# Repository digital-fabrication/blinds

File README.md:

# blinds
Principles of Digital Fabrication, University of Oulu

## Links

- Blinds frame boxes.py url https://www.festi.info/boxes.py/ClosedBox?FingerJoint_angle=90.0&FingerJoint_surroundingspaces=2.0&FingerJoint_edge_width=1.0&FingerJoint_finger=2.0&FingerJoint_play=0.0&FingerJoint_space=2.0&FingerJoint_width=1.0&x=450.0&y=50.0&h=440.0&outside=0&thickness=3.0&format=svg&tabs=0.0&debug=0&reference=100&burn=0.1&render=1
- Manual install instructions for esp32 on Windows (might be useful if you do not have administrative access rights) https://github.com/espressif/arduino-esp32/blob/master/docs/arduino-ide/windows.md

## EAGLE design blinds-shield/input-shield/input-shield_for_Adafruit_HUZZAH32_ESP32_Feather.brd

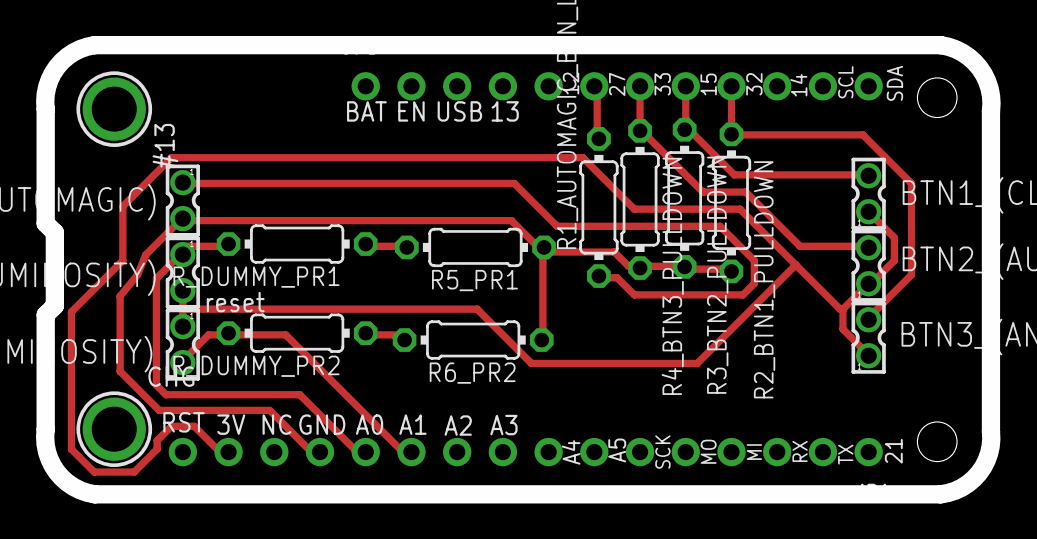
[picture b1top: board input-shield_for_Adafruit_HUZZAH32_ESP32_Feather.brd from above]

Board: 2 copper layers, 52.6 x 25.0 mm, 18 parts (0 on the bottom side), 11 nets.

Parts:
BTN1_(CLOCKWIZE), BTN2_(AUTOMAGIC), BTN3_(ANTICLOCKWIZE): 332-02
JP1: 1X16_ROUND_MIN
JP3: 1X12_ROUND_MIN
LED_(AUTOMAGIC): 332-02
PR1_(LUMINOSITY), PR2_(LUMINOSITY): 332-02
R1_AUTOMAGIC_BTN_LED: 165Ω; 0204/7
R2_BTN1_PULLDOWN, R3_BTN2_PULLDOWN, R4_BTN3_PULLDOWN: 1kΩ; 0204/7
R5_PR1, R6_PR2: 4k ohm; 0204/7
R_DUMMY_PR1, R_DUMMY_PR2: 0k ohm; 0204/7
U$31, U$32: MOUNTINGHOLE2.5; MOUNTINGHOLE_2.5_PLATED

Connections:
3.3V: BTN1_(CLOCKWIZE).1, BTN2_(AUTOMAGIC).1, BTN3_(ANTICLOCKWIZE).1, JP1.15, PR1_(LUMINOSITY).2, PR2_(LUMINOSITY).1
A0_DAC2: JP1.12, PR1_(LUMINOSITY).1, R_DUMMY_PR1.2
A1_DAC1: JP1.11, PR2_(LUMINOSITY).2, R_DUMMY_PR2.2
GND: JP1.13, LED_(AUTOMAGIC).2, R2_BTN1_PULLDOWN.2, R3_BTN2_PULLDOWN.2, R4_BTN3_PULLDOWN.2, R5_PR1.1, R6_PR2.1
IO15_A8: BTN1_(CLOCKWIZE).2, JP3.8, R3_BTN2_PULLDOWN.1
IO27_A10: JP3.6, R1_AUTOMAGIC_BTN_LED.2
IO32_A7: BTN3_(ANTICLOCKWIZE).2, JP3.9, R2_BTN1_PULLDOWN.1
IO33_A9: BTN2_(AUTOMAGIC).2, JP3.7, R4_BTN3_PULLDOWN.1
unnamed: LED_(AUTOMAGIC).1, R1_AUTOMAGIC_BTN_LED.1
unnamed: R5_PR1.2, R_DUMMY_PR1.1
unnamed: R6_PR2.2, R_DUMMY_PR2.1

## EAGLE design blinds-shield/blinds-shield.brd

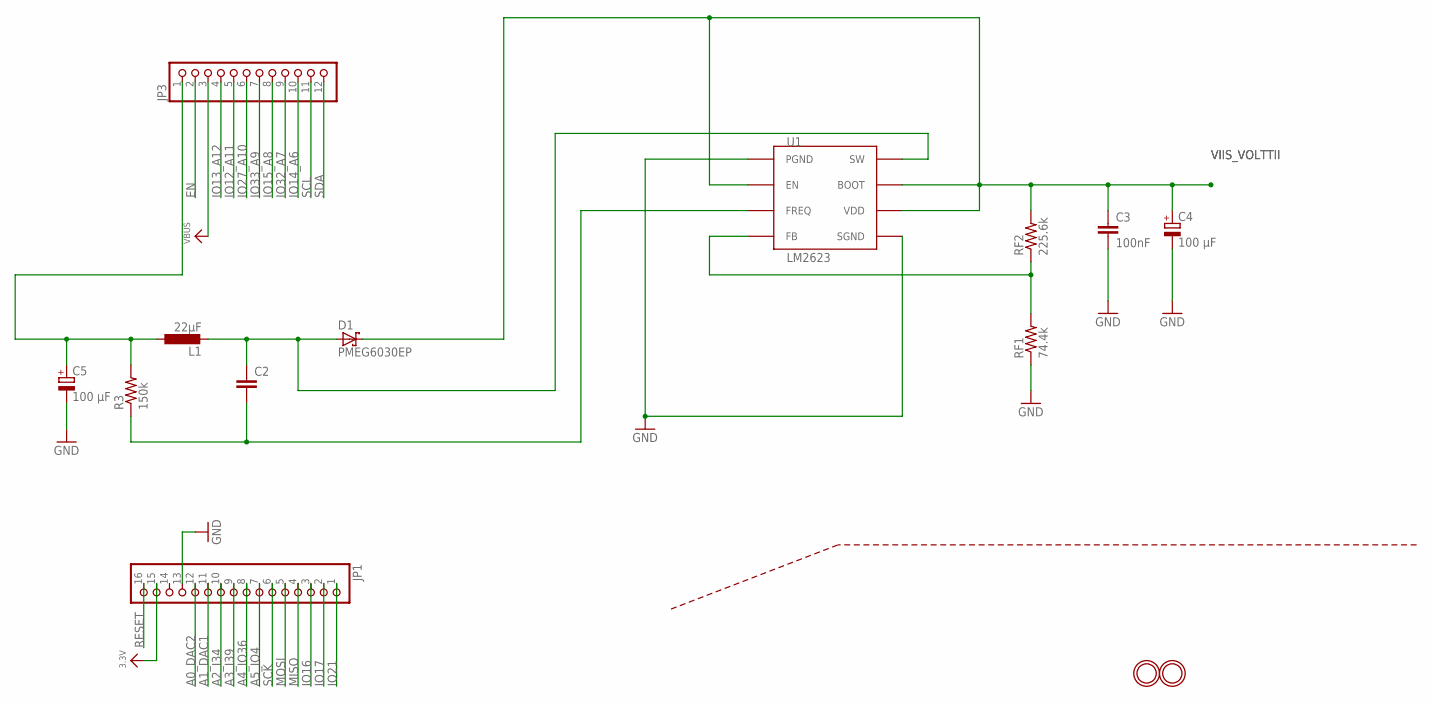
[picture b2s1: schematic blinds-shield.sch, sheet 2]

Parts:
C2: C-EU025-060X050; C025-060X050
C3: 100nF; C025-060X050
C4, C5: 100 µF; 085CS_1AR
D1: PMEG6030EP; SOD128
JP1: HEADER-1X16_MIN; 1X16_ROUND_MIN
JP3: HEADER-1X12_MIN; 1X12_ROUND_MIN
L1: 22µF; L5650M
R3: 150k; R5025
RF1: 74.4k; R5025
RF2: 225.6k; R5025
U1: LM2623; VSSOP8
U$31, U$32: MOUNTINGHOLE2.5; MOUNTINGHOLE_2.5_PLATED

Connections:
3.3V: JP1.15
A0_DAC2: JP1.12
A1_DAC1: JP1.11
A2_I34: JP1.10
A3_I39: JP1.9
A4_IO36: JP1.8
A5_IO4: JP1.7
EN: JP3.2
GND: C3.2, C4.-, C5.-, JP1.13, RF1.1, U1.PGND, U1.SGND
IO12_A11: JP3.5
IO13_A12: JP3.4
IO14_A6: JP3.10
IO15_A8: JP3.8
IO16: JP1.3
IO17: JP1.2
IO21: JP1.1
IO27_A10: JP3.6
IO32_A7: JP3.9
IO33_A9: JP3.7
MISO: JP1.4
MOSI: JP1.5
unnamed: C5.+, JP3.1, L1.1, R3.2
unnamed: C2.1, D1.2 (A), L1.2, U1.SW
unnamed: C2.2, R3.1, U1.FREQ
unnamed: RF1.2, RF2.1, U1.FB
RESET: JP1.16
SCK: JP1.6
SCL: JP3.11
SDA: JP3.12
VBUS: JP3.3
VIIS_VOLTTII: C3.1, C4.+, D1.1 (K), RF2.2, U1.BOOT, U1.EN, U1.VDD

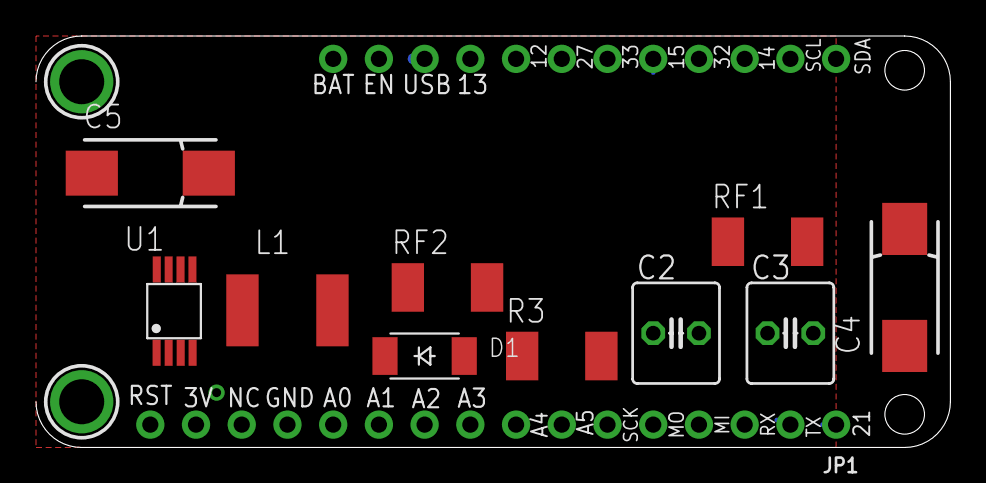
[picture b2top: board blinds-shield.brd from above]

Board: 2 copper layers, 50.8 x 22.9 mm, 14 parts (0 on the bottom side), 6 nets.

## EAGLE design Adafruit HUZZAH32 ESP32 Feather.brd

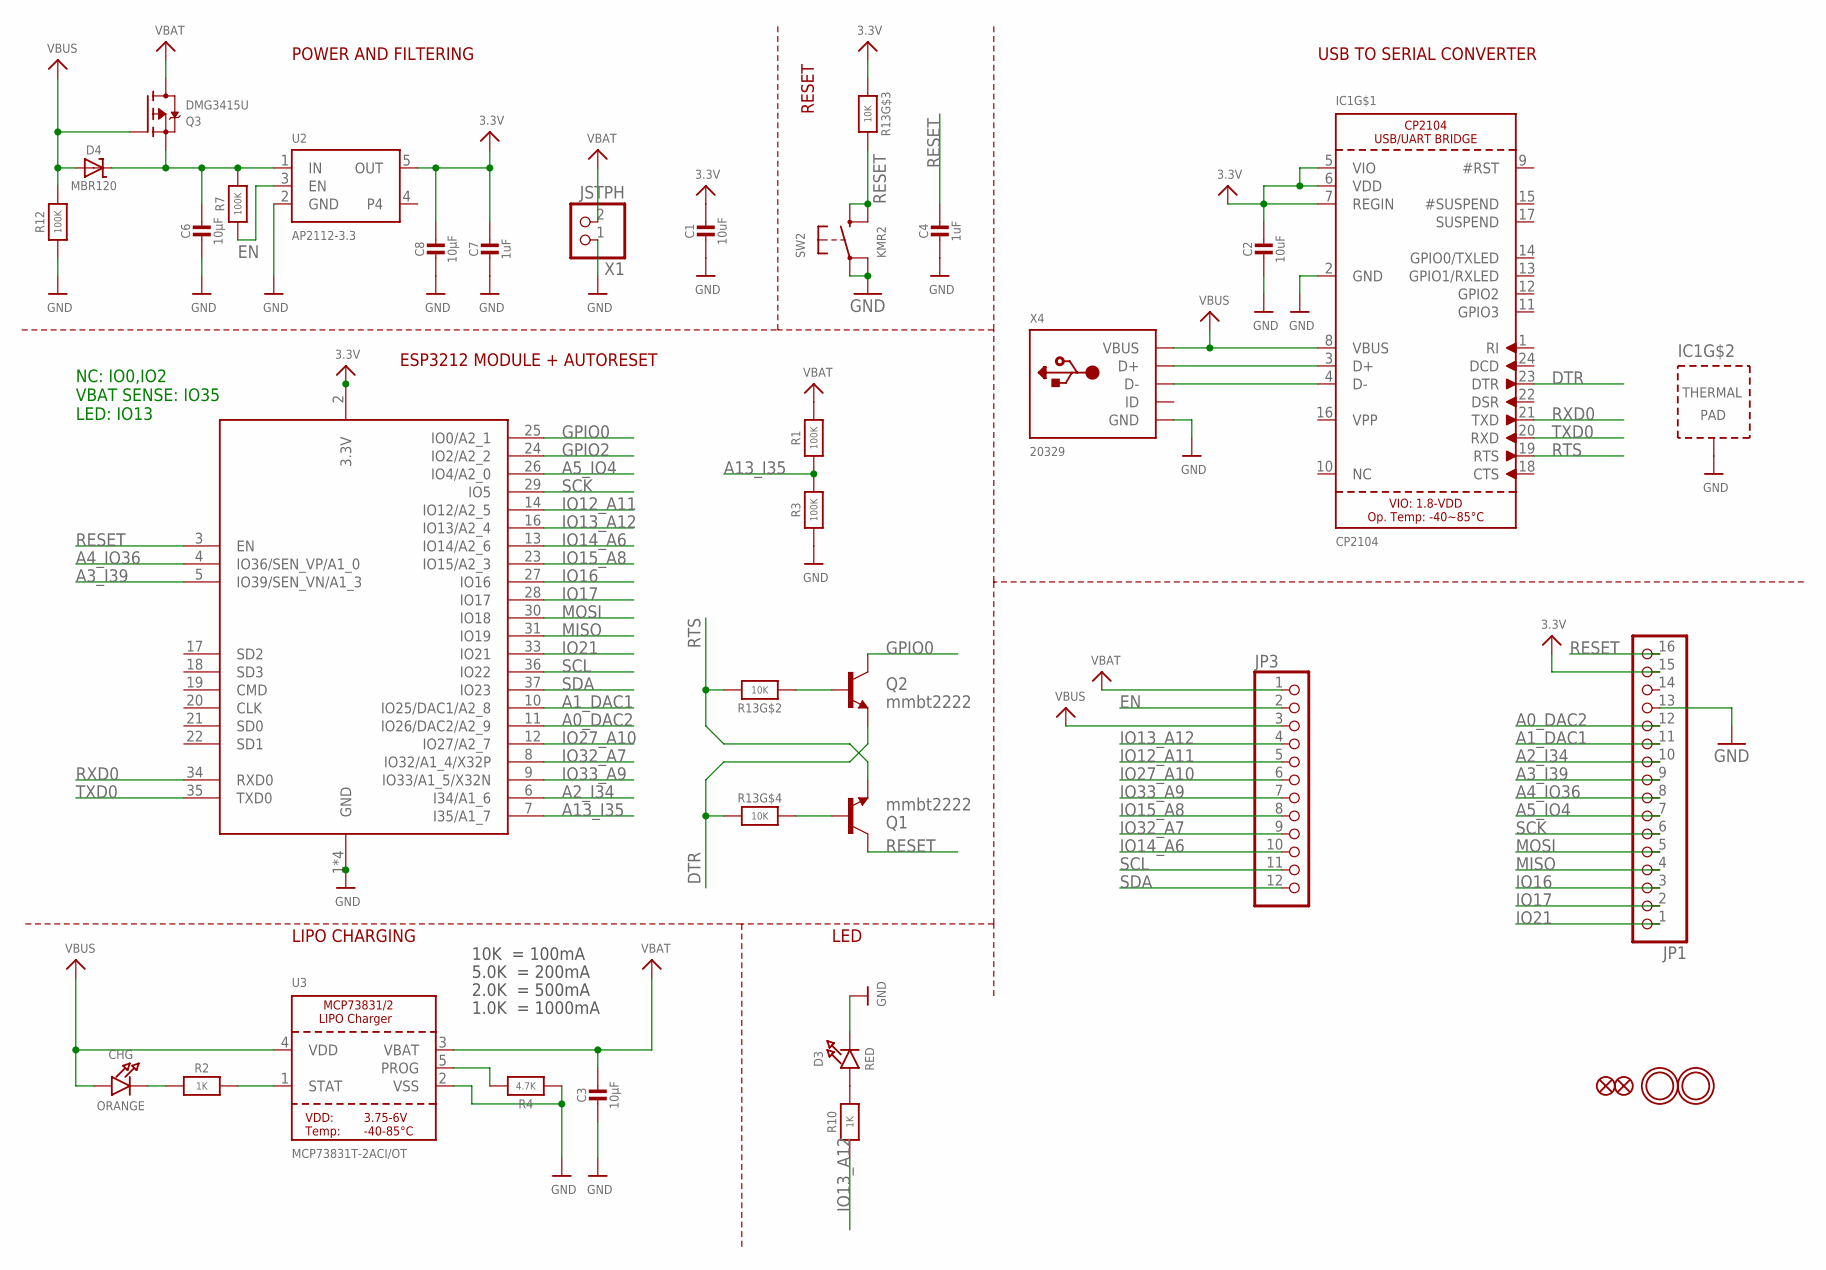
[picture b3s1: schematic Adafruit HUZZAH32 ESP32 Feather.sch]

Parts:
C1, C2: 10uF; 0805-NO
C3, C6, C8: 10µF; 0805-NO
C4, C7: 1uF; 0603-NO
CHG: ORANGE; CHIPLED_0805_NOOUTLINE
D3: RED; CHIPLED_0805_NOOUTLINE
D4: MBR120; SOD-123
IC1: CP2104; QFN24_4MM_SMSC
JP1: HEADER-1X16_MIN; 1X16_ROUND_MIN
JP3: HEADER-1X12_MIN; 1X12_ROUND_MIN
Q1, Q2: mmbt2222; SOT23-3
Q3: DMG3415U; SOT23-R
R1, R3, R7, R12: 100K; 0603-NO
R2, R10: 1K; 0603-NO
R4: 4.7K; 0603-NO
R13: 10K; RESPACK_4X0603
SW2: KMR2; BTN_KMR2_4.6X2.8
U2: AP2112-3.3; SOT23-5
U3: MCP73831T-2ACI/OT; SOT23-5
U$31, U$32: MOUNTINGHOLE2.5; MOUNTINGHOLE_2.5_PLATED
U$34, U$35: FIDUCIAL_1MM
X1: JSTPH; JSTPH2
X2: ESP32_WROOM32_SKINNY; WROOM32_SKINNY
X4: 20329; 4UCONN_20329_V2

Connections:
3.3V: C1.1, C2.1, C7.1, C8.1, IC1.5 (VIO), IC1.6 (VDD), IC1.7 (REGIN), JP1.15, R13.3 (1), U2.5 (OUT), X2.2 (3.3V)
A0_DAC2: JP1.12, X2.11 (IO26/DAC2/A2_9)
A1_DAC1: JP1.11, X2.10 (IO25/DAC1/A2_8)
A2_I34: JP1.10, X2.6 (I34/A1_6)
A3_I39: JP1.9, X2.5 (IO39/SEN_VN/A1_3)
A4_IO36: JP1.8, X2.4 (IO36/SEN_VP/A1_0)
A5_IO4: JP1.7, X2.26 (IO4/A2_0)
A13_I35: R1.1, R3.2, X2.7 (I35/A1_7)
DTR: IC1.23 (DTR), Q2.2 (E), R13.4 (1)
EN: JP3.2, R7.1, U2.3 (EN)
GND: C1.2, C2.2, C3.2, C4.2, C6.2, C7.2, C8.2, D3.C, IC1.2 (GND), IC1.THERM (TP), JP1.13, R3.1, R4.1, R12.1, SW2.A, SW2.A' (P1), U2.2 (GND), U3.2 (VSS), X1.1, X2.1 (GND), X2.15 (GND), X2.38 (GND), X2.P$1 (GND), X4.BASE@1 (GND), X4.BASE@2 (GND), X4.GND, X4.SPRT@1 (GND), X4.SPRT@2 (GND), X4.SPRT@3 (GND), X4.SPRT@4 (GND)
GPIO0: Q2.3 (C), X2.25 (IO0/A2_1)
GPIO2: X2.24 (IO2/A2_2)
IO12_A11: JP3.5, X2.14 (IO12/A2_5)
IO13_A12: JP3.4, R10.1, X2.16 (IO13/A2_4)
IO14_A6: JP3.10, X2.13 (IO14/A2_6)
IO15_A8: JP3.8, X2.23 (IO15/A2_3)
IO16: JP1.3, X2.27 (IO16)
IO17: JP1.2, X2.28 (IO17)
IO21: JP1.1, X2.33 (IO21)
IO27_A10: JP3.6, X2.12 (IO27/A2_7)
IO32_A7: JP3.9, X2.8 (IO32/A1_4/X32P)
IO33_A9: JP3.7, X2.9 (IO33/A1_5/X32N)
MISO: JP1.4, X2.31 (IO19)
MOSI: JP1.5, X2.30 (IO18)
unnamed: CHG.C, R2.1
unnamed: IC1.3 (D+), X4.D+
unnamed: R2.2, U3.1 (STAT)
unnamed: R4.2, U3.5 (PROG)
unnamed: D3.A, R10.2
unnamed: IC1.4 (D-), X4.D-
unnamed: C6.1, D4.C, Q3.2 (S), R7.2, U2.1 (IN)
unnamed: Q1.1 (B), R13.5 (2)
unnamed: Q2.1 (B), R13.2 (1)
RESET: C4.1, JP1.16, Q1.3 (C), R13.6 (2), SW2.B (S), SW2.B' (S1), X2.3 (EN)
RTS: IC1.19 (RTS), Q1.2 (E), R13.7 (2)
RXD0: IC1.21 (TXD), X2.34 (RXD0)
SCK: JP1.6, X2.29 (IO5)
SCL: JP3.11, X2.36 (IO22)
SDA: JP3.12, X2.37 (IO23)
TXD0: IC1.20 (RXD), X2.35 (TXD0)
VBAT: C3.1, JP3.1, Q3.3 (D), R1.2, U3.3 (VBAT), X1.2
VBUS: CHG.A, D4.A, IC1.8 (VBUS), JP3.3, Q3.1 (G), R12.2, U3.4 (VDD), X4.VBUS

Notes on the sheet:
POWER AND FILTERING
RESET
10K = 100mA
5.0K = 200mA
2.0K = 500mA
1.0K = 1000mA
USB TO SERIAL CONVERTER
LIPO CHARGING
LED
ESP3212 MODULE + AUTORESET
NC: IO0,IO2 VBAT SENSE: IO35 LED: IO13

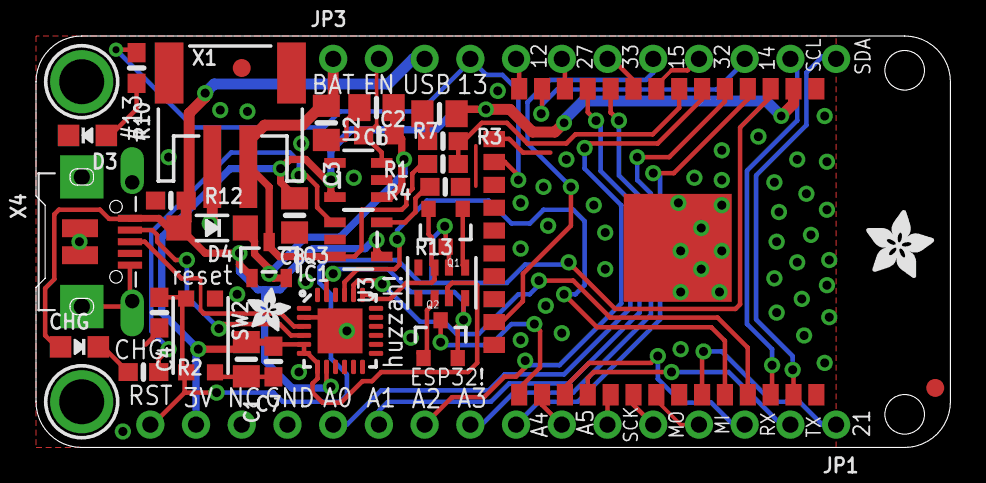
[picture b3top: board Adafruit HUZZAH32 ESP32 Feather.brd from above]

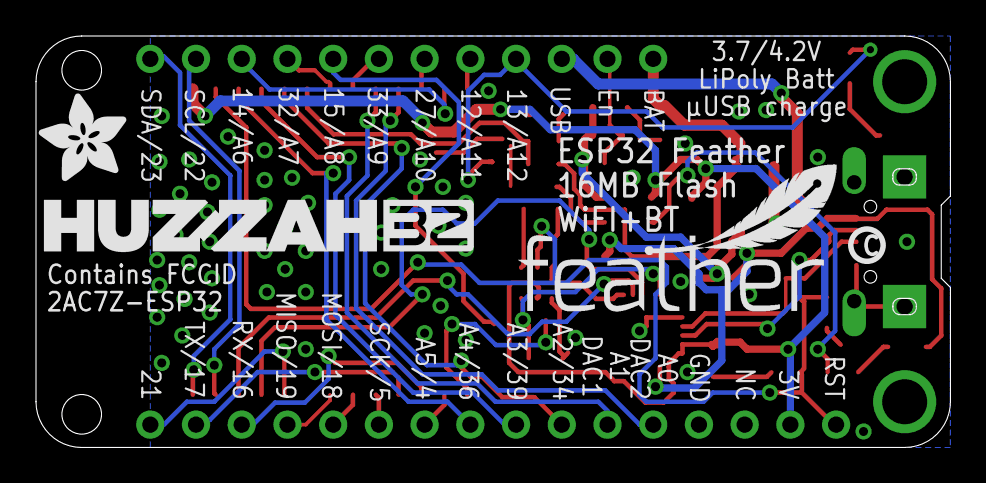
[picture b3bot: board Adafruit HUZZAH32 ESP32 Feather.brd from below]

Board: 2 copper layers, 50.8 x 22.9 mm, 40 parts (4 on the bottom side), 42 nets.

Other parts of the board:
U$7: ADAFRUIT_5MM
U$9: FEATHERLOGO_MED
U$13: PCBFEAT-REV-040
U$14: ADAFRUIT_2.5MM
U$15: ADAFRUIT_3.5MM
U$43: HUZZAH32

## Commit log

2019-03-20 Blinds frame stuff
2019-03-21 Red -> black, add space between filling pieces
2019-04-16 Rename source.ino to source2.ino
2019-04-23 Svg files for the box
2019-04-23 motorbox added
2019-04-23 new motorbox file added
2019-04-23 black line colors and usb hole added
2019-04-23 Added Blinds-Motorbox.pdf
    Were used on epilog laserfusion
2019-04-24 koppa laser cut added
2019-04-24 updated koppa
2019-04-28 Deleted old versions of blindsframe
2019-04-28 Rename and move frame
2019-04-28 Rename and move original adafruit board and schematics
2019-04-28 Moved small amount of textual content straight to README.md
2019-04-28 Removed one more version of blinds-frame
2019-04-28 mv & rn
2019-04-30 Added basics of input-shield
2019-05-02 shield stuff
2019-05-02 Routing attempts
2019-05-02 Add files via upload
    nu shieeeld
2019-05-02 Add files via upload
    updated routes-and-pads-cropped.png, added all rml files
2019-05-02 Add files via upload
    A0 and A1 are now connected to photoresistors.
2019-05-02 Add files via upload
    Moved some lines.

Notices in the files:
parts and their libraries:
microbuilder: This work is placed in the public domain, and may be freely used for commercial and non-commercial work with the following conditions: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
SparkFun: Licensing: CC v3.0 Share-Alike You are welcome to use this library for commercial purposes.
